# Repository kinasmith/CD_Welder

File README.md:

##Capacitive Discharge Welder

based off of this [project.](http://www.instructables.com/id/Capacitive-Discharge-CD-Welder-for-battery-tabs/) and this [project](http://zeva.com.au/Projects/SpotWelderV2/). 

Included in this repo is the Control code (for arduino Pro Mini), and the PCB files I used. The Capacitor Board is slightly too large for the free version of Eagle (sorry!).

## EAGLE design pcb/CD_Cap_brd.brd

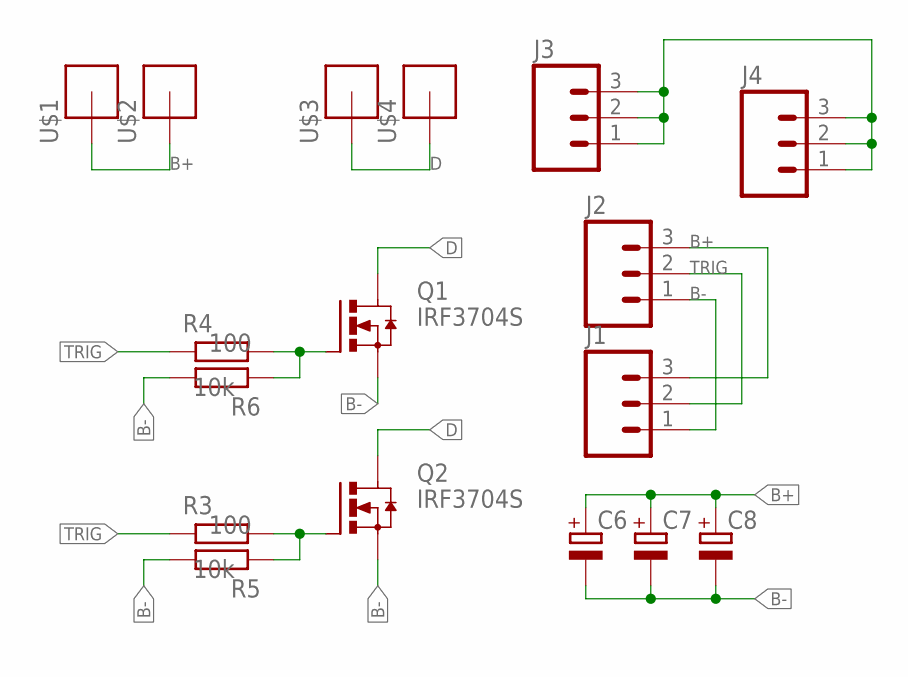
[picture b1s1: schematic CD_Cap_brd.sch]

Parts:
C6, C7, C8: CPOL-EUE10-35; EB35D
J1, J2: M03PTH; 1X03
J3, J4: M03LOCK; 1X03_LOCK
Q1, Q2: IRF3704S; D2PACK
R3, R4: 100; R0603-N
R5, R6: 10k; R0603-N
U$1, U$2, U$3, U$4: BIG_PINHEADX110-32; M6_PINHEAD

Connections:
B+: C6.+, C7.+, C8.+, J1.3, J2.3, U$1.P$1, U$2.P$1
B-: C6.-, C7.-, C8.-, J1.1, J2.1, J3.1, J3.2, J3.3, J4.1, J4.2, J4.3, Q1.3 (S), Q2.3 (S), R5.2, R6.2
D: Q1.2 (D), Q2.2 (D), U$3.P$1, U$4.P$1
unnamed: Q1.1 (G), R4.2, R6.1
unnamed: Q2.1 (G), R3.2, R5.1
TRIG: J1.2, J2.2, R3.1, R4.1

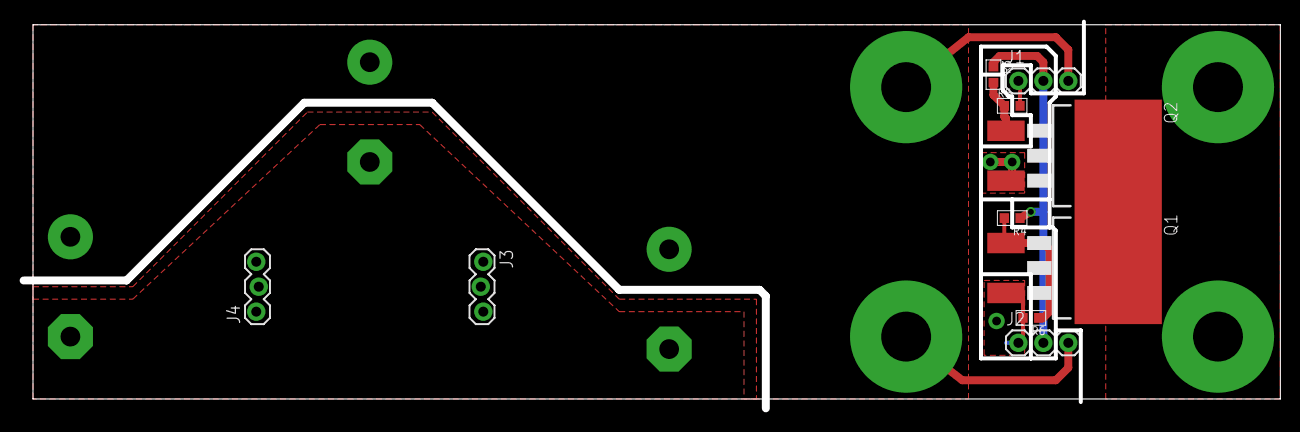
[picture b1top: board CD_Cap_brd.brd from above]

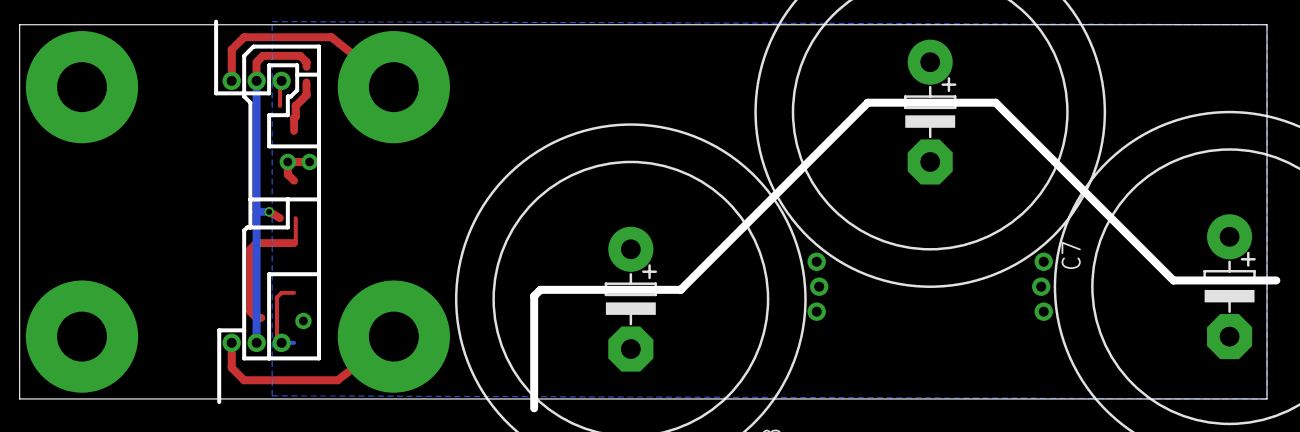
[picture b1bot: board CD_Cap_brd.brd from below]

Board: 2 copper layers, 127.5 x 39.2 mm, 17 parts (3 on the bottom side), 6 nets.

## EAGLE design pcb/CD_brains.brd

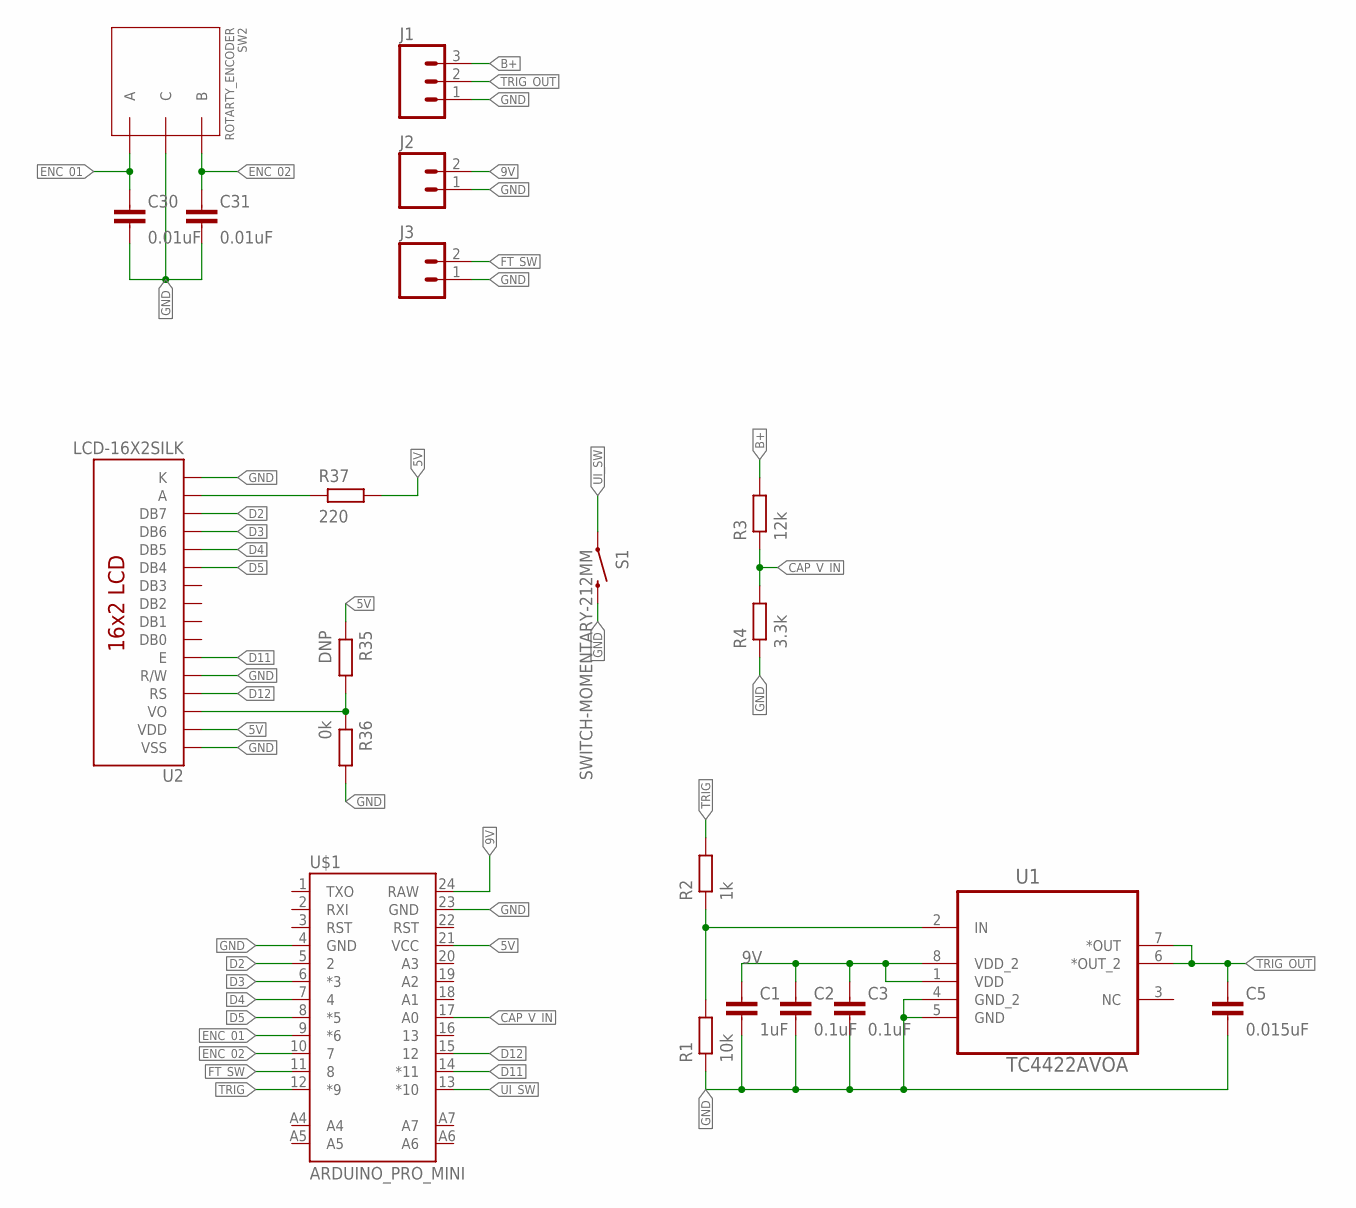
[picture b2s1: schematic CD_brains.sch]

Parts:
C1: 1uF; C0805-N
C2, C3: 0.1uF; C0603-N
C5: 0.015uF; C0603-N
C30, C31: 0.01uF; C0603-N
J1: M03LOCK_NO_SILK; 1X03_LOCK_NO_SILK
J2, J3: M02LOCK; 1X02_LOCK
R1: 10k; R0603-N
R2: 1k; R0603-N
R3: 12k; R0603-N
R4: 3.3k; R0603-N
R35: DNP; R0603-N
R36: 0k; R0603-N
R37: 220; R0603-N
S1: SWITCH-MOMENTARY-212MM; TACTILE-PTH-12MM
SW2: ROTARTY_ENCODER; ROTARY_ENC_PLAIN
U1: TC4422AVOA; SOIC127P600X175-8N
U2: LCD-16X2SILK; LCD-16X2
U$1: ARDUINO_PRO_MINI

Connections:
5V: R35.1, R37.2, U2.2 (VDD), U$1.21 (VCC)
9V: C1.1, C2.1, C3.1, J2.2, U1.1 (VDD), U1.8 (VDD_2), U$1.24 (RAW)
B+: J1.3, R3.2
CAP_V_IN: R3.1, R4.2, U$1.17 (A0)
D2: U2.14 (DB7), U$1.5 (2)
D3: U2.13 (DB6), U$1.6 (*3)
D4: U2.12 (DB5), U$1.7 (4)
D5: U2.11 (DB4), U$1.8 (*5)
D11: U2.6 (E), U$1.14 (*11)
D12: U2.4 (RS), U$1.15 (12)
ENC_01: C30.1, SW2.A, U$1.9 (*6)
ENC_02: C31.1, SW2.B, U$1.10 (7)
FT_SW: J3.2, U$1.11 (8)
GND: C1.2, C2.2, C3.2, C5.2, C30.2, C31.2, J1.1, J2.1, J3.1, R1.1, R4.1, R36.2, S1.3 (2), SW2.C, U1.4 (GND_2), U1.5 (GND), U2.1 (VSS), U2.5 (R/W), U2.16 (K), U$1.4 (GND), U$1.23 (GND)
unnamed: R1.2, R2.1, U1.2 (IN)
unnamed: R37.1, U2.15 (A)
unnamed: R35.2, R36.1, U2.3 (VO)
TRIG: R2.2, U$1.12 (*9)
TRIG_OUT: C5.1, J1.2, U1.6 (*OUT_2), U1.7 (*OUT)
UI_SW: S1.1, U$1.13 (*10)

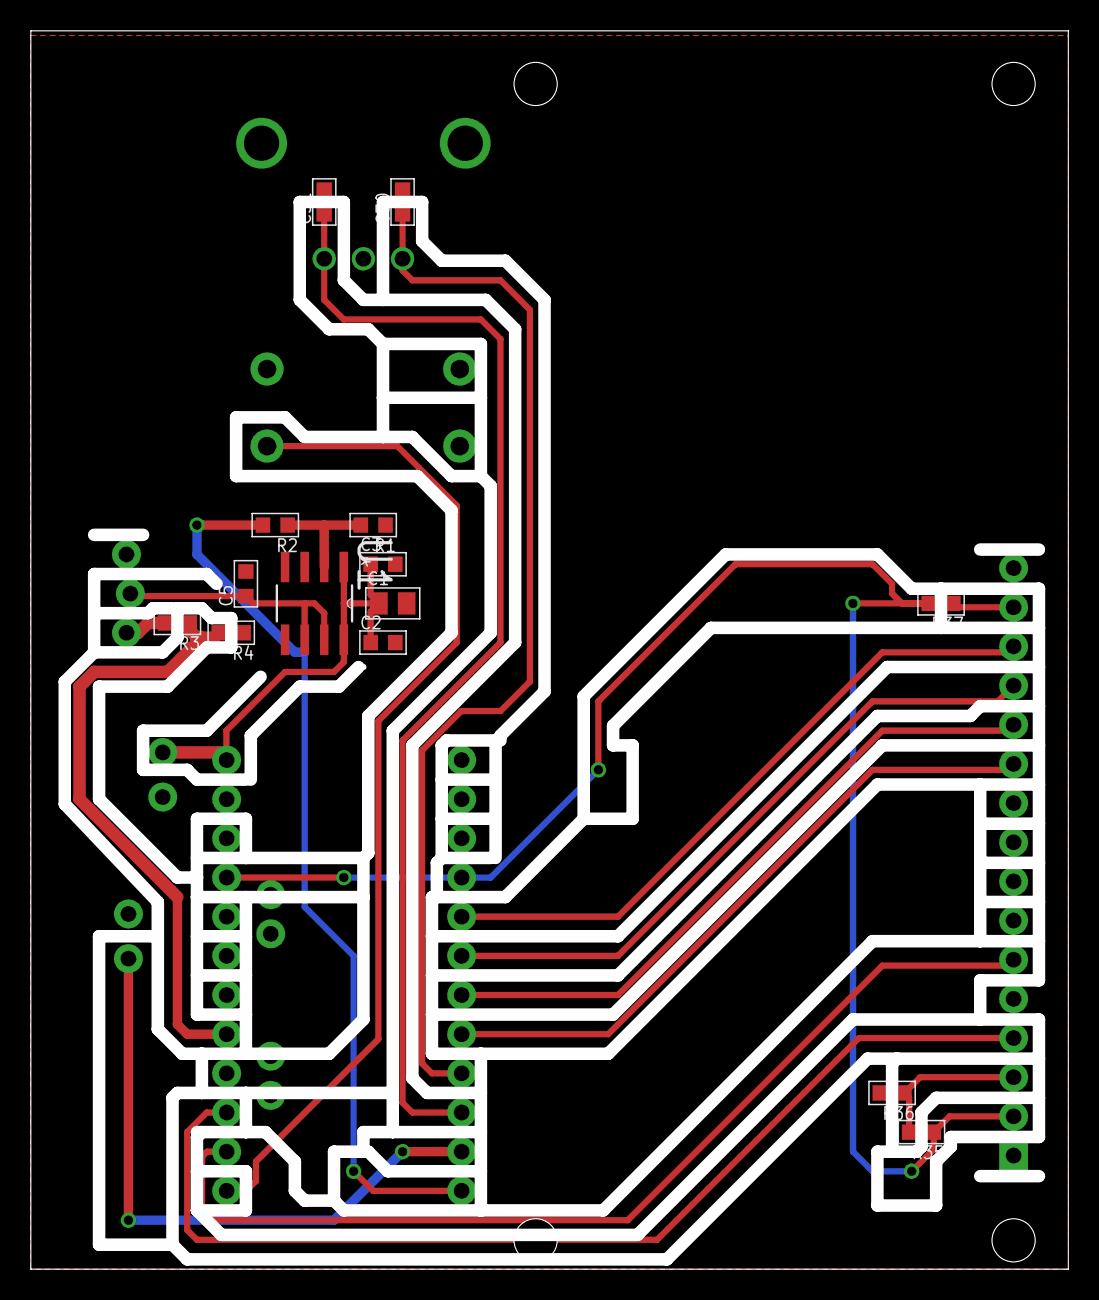
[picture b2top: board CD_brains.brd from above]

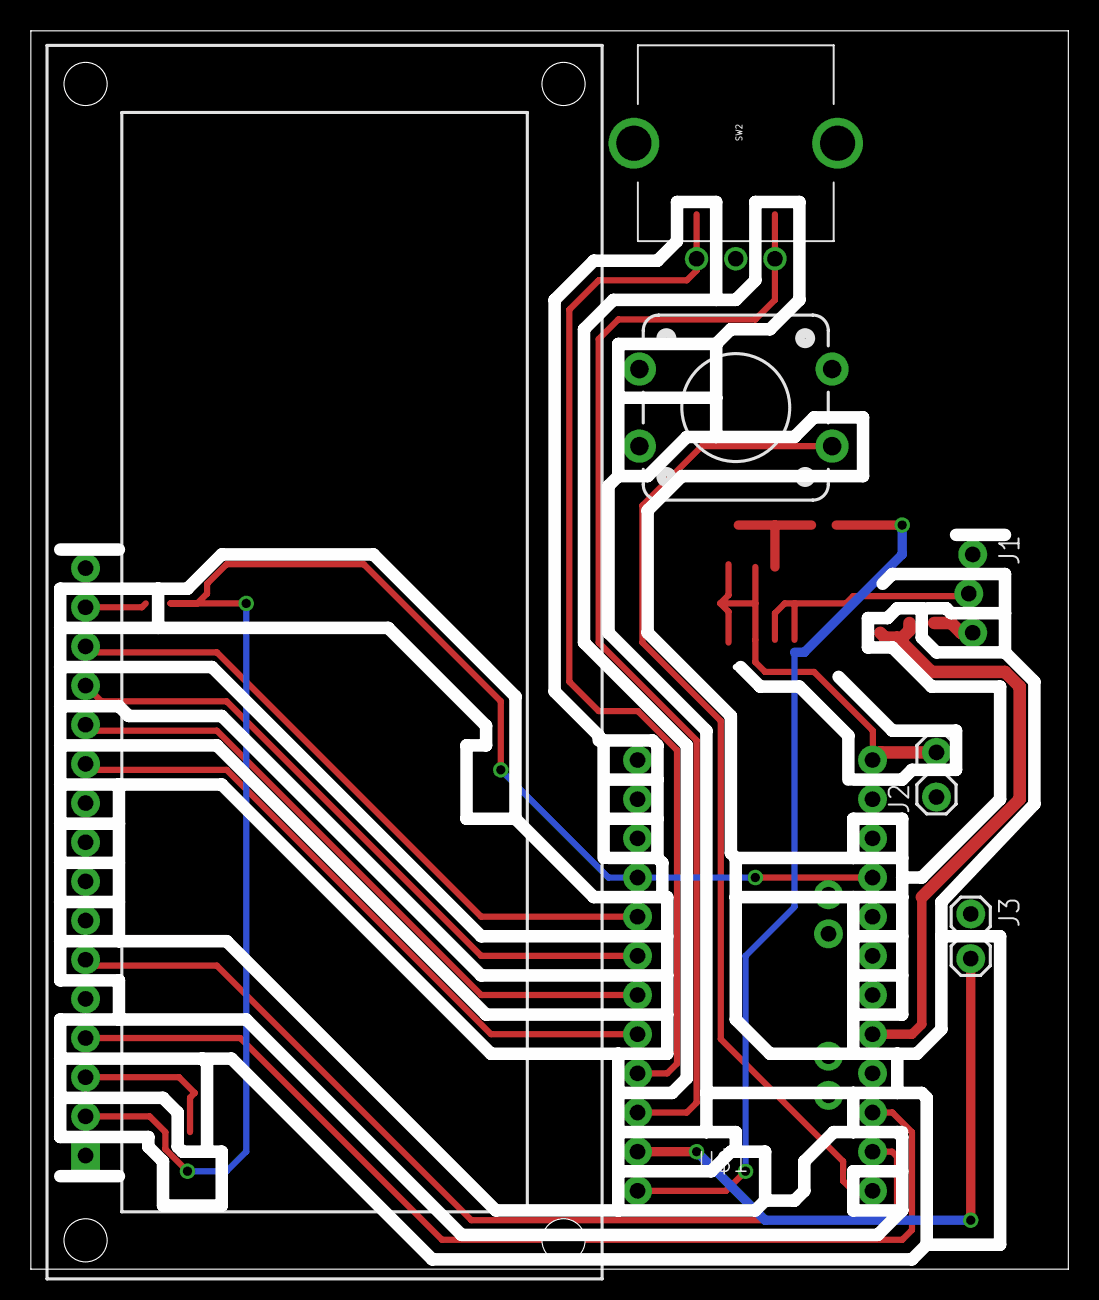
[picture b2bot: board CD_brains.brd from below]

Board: 2 copper layers, 66.5 x 79.5 mm, 21 parts (7 on the bottom side), 20 nets.

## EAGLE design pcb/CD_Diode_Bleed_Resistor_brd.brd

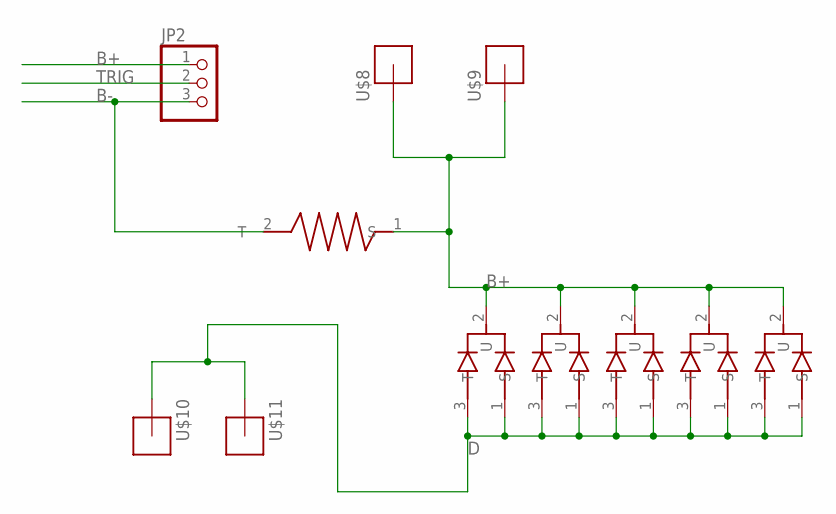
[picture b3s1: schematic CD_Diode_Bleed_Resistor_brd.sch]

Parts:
JP2: PINHD-1X3/90; 1X03/90
U$1, U$2, U$3, U$4, U$5: STTH6002CW; TO-247
U$7: RESISTOR_5W_1INCH; RESISTOR_1INCH_5W
U$8, U$9, U$10, U$11: BIG_PINHEADX110-32; M6_PINHEAD

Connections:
B+: JP2.1, U$1.2 (U), U$2.2 (U), U$3.2 (U), U$4.2 (U), U$5.2 (U), U$7.1 (S), U$8.P$1, U$9.P$1
B-: JP2.3, U$7.2 (T)
D: U$1.1 (S), U$1.3 (T), U$2.1 (S), U$2.3 (T), U$3.1 (S), U$3.3 (T), U$4.1 (S), U$4.3 (T), U$5.1 (S), U$5.3 (T), U$10.P$1, U$11.P$1
TRIG: JP2.2

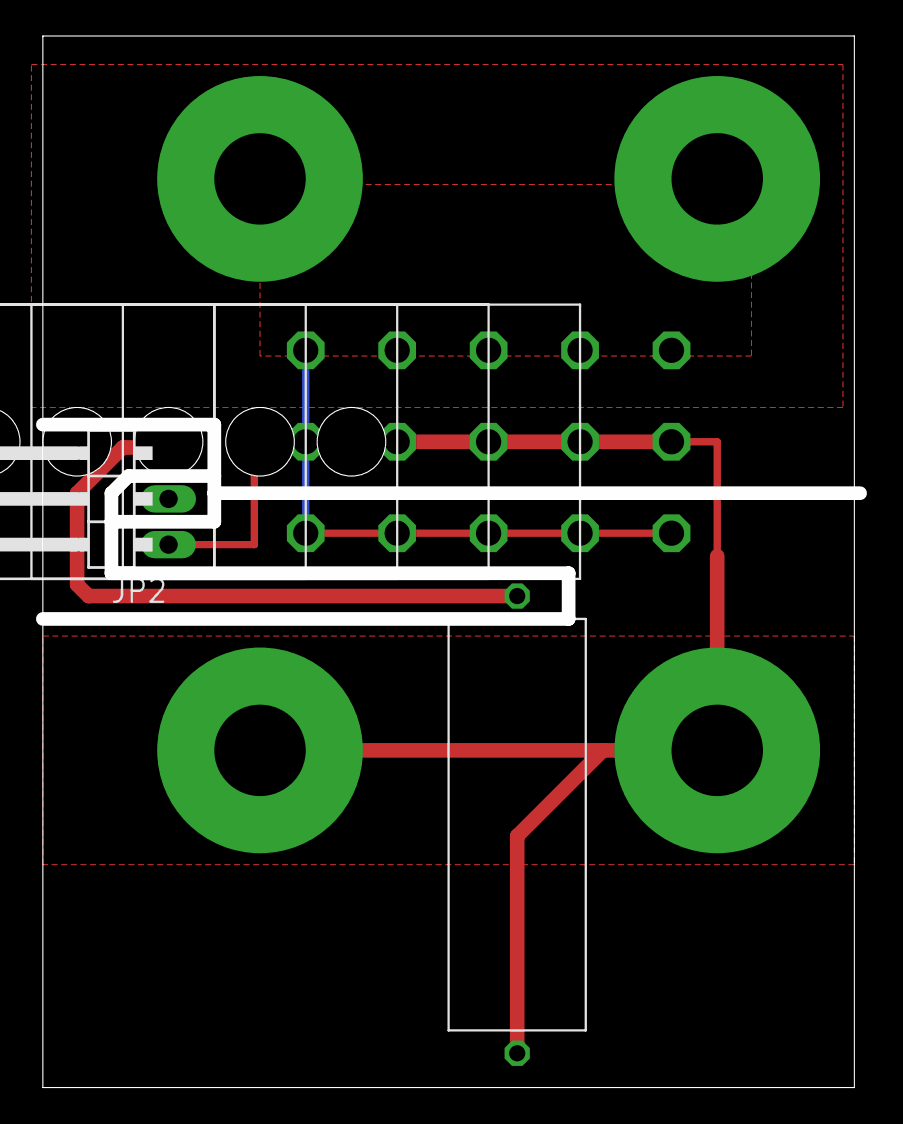
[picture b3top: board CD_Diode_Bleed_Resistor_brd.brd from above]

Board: 2 copper layers, 45.4 x 57.7 mm, 11 parts (0 on the bottom side), 3 nets.

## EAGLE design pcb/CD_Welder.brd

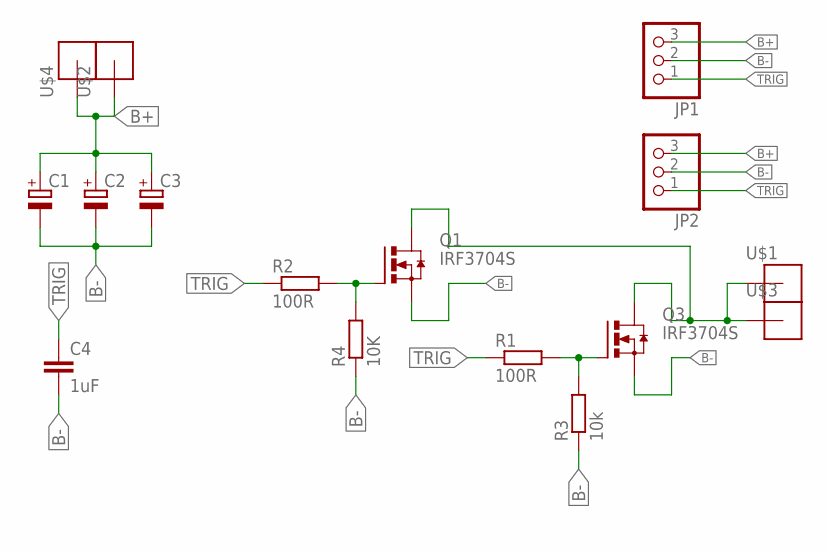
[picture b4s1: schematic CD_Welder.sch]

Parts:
C1, C2, C3: CPOL-EUE10-30; EB30D
C4: 1uF; C1206
JP1, JP2: PINHD-1X3; 1X03
Q1, Q3: IRF3704S; D2PACK
R1, R2: 100R; R1206
R3: 10k; R1206
R4: 10K; R1206
U$1, U$2, U$3, U$4: BIG_PINHEADX1M4; M4_PINHEAD

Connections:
B+: C1.+, C2.+, C3.+, JP1.3, JP2.3, U$2.P$1, U$4.P$1
B-: C1.-, C2.-, C3.-, C4.2, JP1.2, JP2.2, Q1.3 (S), Q3.3 (S), R3.1, R4.1
unnamed: Q1.2 (D), Q3.2 (D), U$1.P$1, U$3.P$1
unnamed: Q1.1 (G), R2.2, R4.2
unnamed: Q3.1 (G), R1.2, R3.2
TRIG: C4.1, JP1.1, JP2.1, R1.1, R2.1

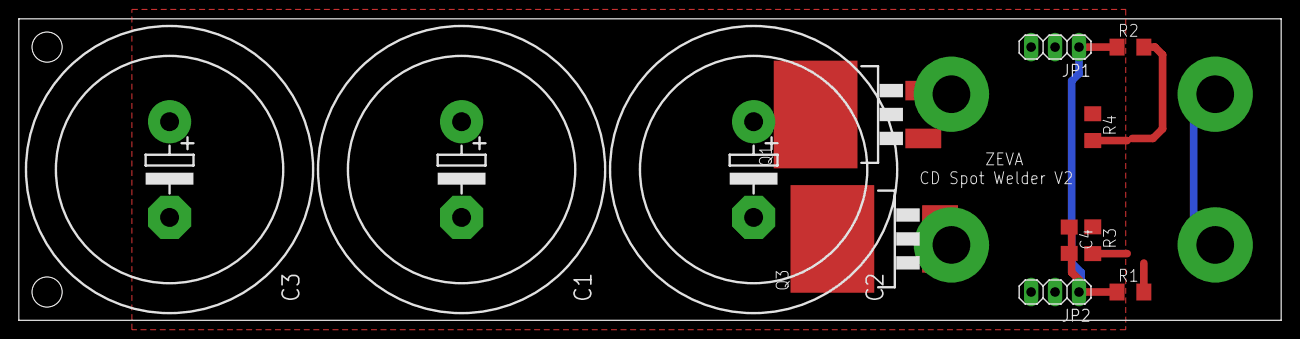
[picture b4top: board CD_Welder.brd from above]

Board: 2 copper layers, 134.0 x 32.0 mm, 16 parts (0 on the bottom side), 6 nets.

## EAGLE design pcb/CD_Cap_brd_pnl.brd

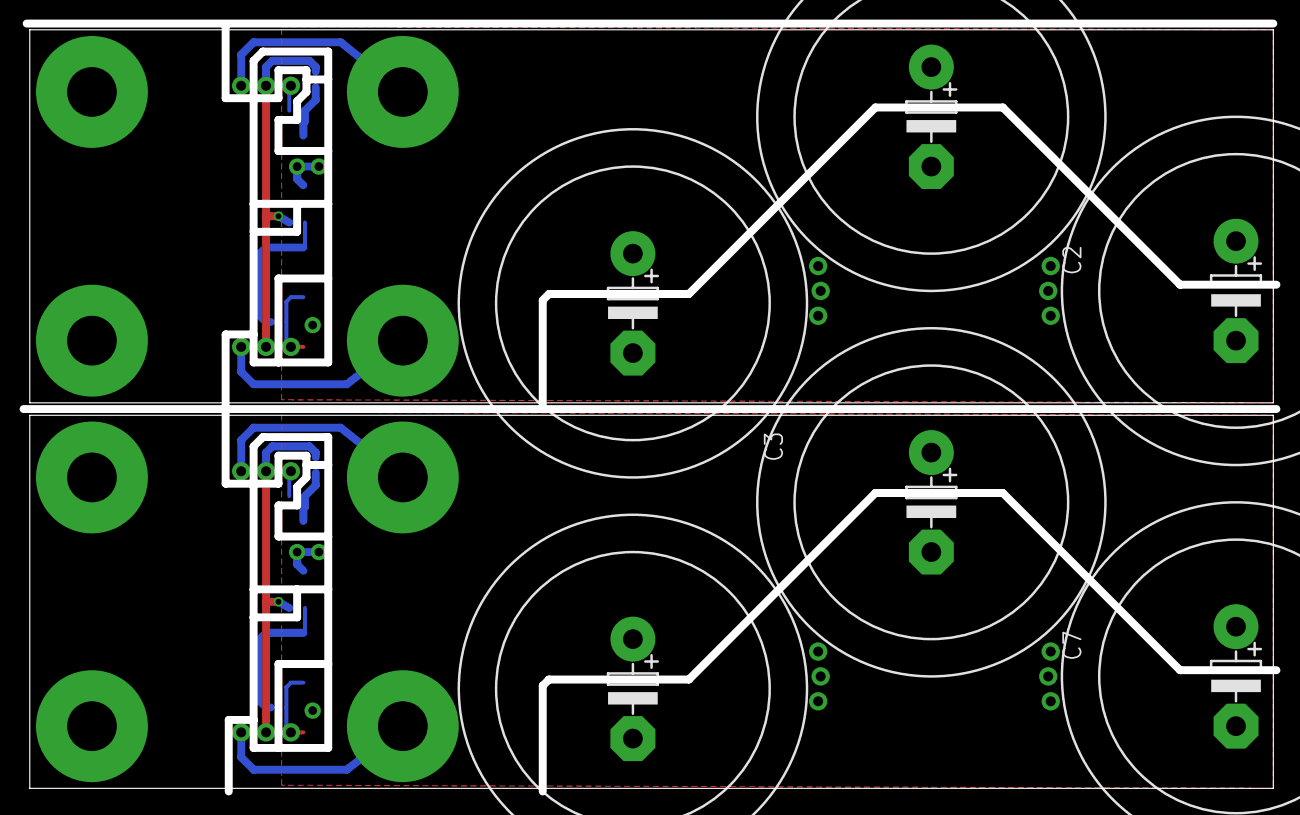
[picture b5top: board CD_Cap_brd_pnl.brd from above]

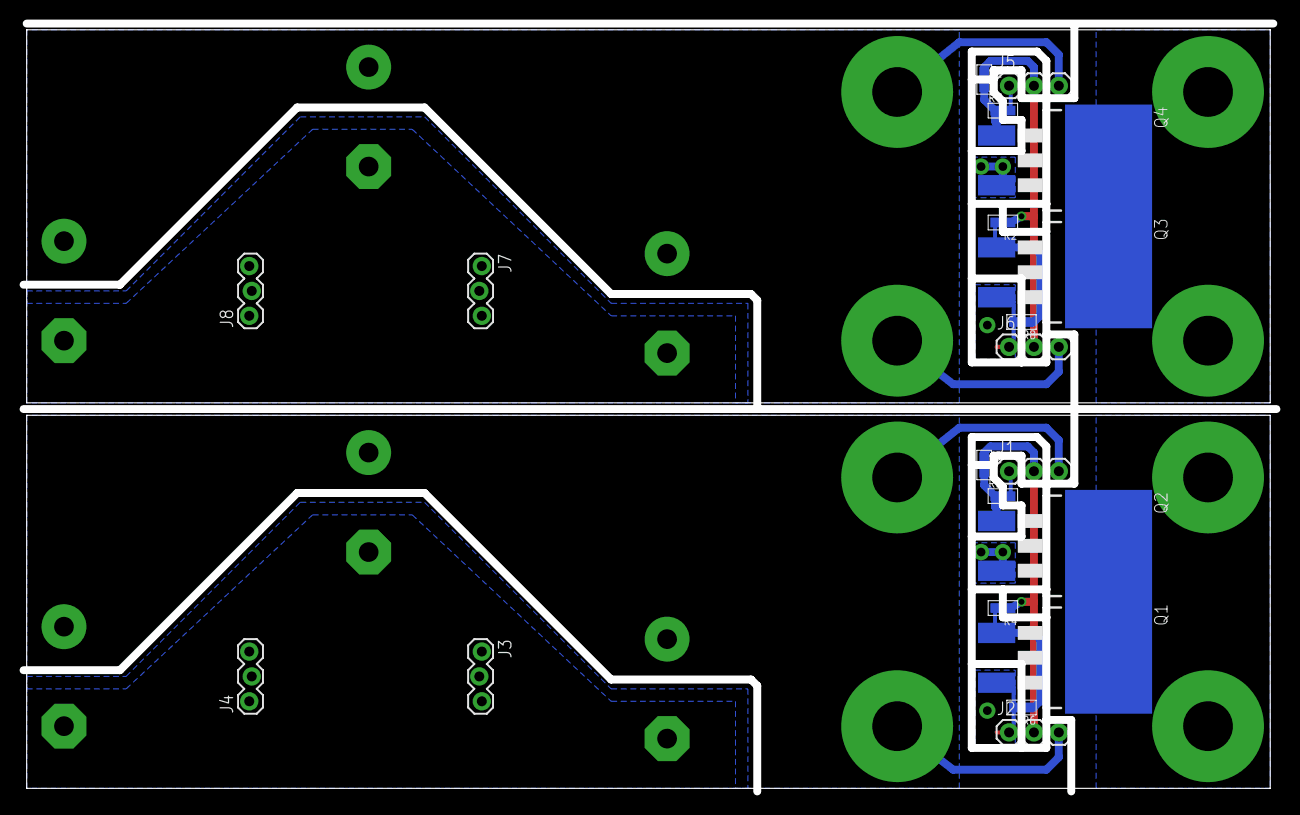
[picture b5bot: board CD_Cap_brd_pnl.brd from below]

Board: 2 copper layers, 128.0 x 78.4 mm, 34 parts (28 on the bottom side), 12 nets.

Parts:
C1, C2, C3, C6, C7, C8: EB35D
J1, J2, J5, J6: 1X03
J3, J4, J7, J8: 1X03_LOCK
Q1, Q2, Q3, Q4: IRF3704S; D2PACK
R1, R2, R3, R4: 100; R0603-N
R5, R6, R7, R8: 10k; R0603-N
U$1, U$2, U$3, U$4, U$5, U$6, U$7, U$8: BIG_PINHEADX110-32; M6_PINHEAD

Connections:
B+: C6.+, C7.+, C8.+, J1.3, J2.3, U$1.P$1, U$2.P$1
B+1: C1.+, C2.+, C3.+, J5.3, J6.3, U$5.P$1, U$6.P$1
B-: C6.-, C7.-, C8.-, J1.1, J2.1, J3.1, J3.2, J3.3, J4.1, J4.2, J4.3, Q1.3, Q2.3, R5.2, R6.2
B-1: C1.-, C2.-, C3.-, J5.1, J6.1, J7.1, J7.2, J7.3, J8.1, J8.2, J8.3, Q3.3, Q4.3, R7.2, R8.2
D: Q1.2, Q2.2, U$3.P$1, U$4.P$1
D1: Q3.2, Q4.2, U$7.P$1, U$8.P$1
unnamed: Q1.1, R4.2, R6.1
unnamed: Q4.1, R1.2, R7.1
unnamed: Q2.1, R3.2, R5.1
unnamed: Q3.1, R2.2, R8.1
TRIG: J1.2, J2.2, R3.1, R4.1
TRIG1: J5.2, J6.2, R1.1, R2.1

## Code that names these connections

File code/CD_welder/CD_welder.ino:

#define ENCODER_DO_NOT_USE_INTERRUPTS

#include "Encoder.h"
#include "LiquidCrystal.h"
#include "Bounce2.h"

const int UI_SW = 10;
const int FT_SW = 8;
const int LED = 13;
const int CAP_V_INPUT = 0;
const int TRIG = 9;
const float div_z1_val = 11990;
const float div_z2_val = 3227;

//vOut = z2/(z1+z2) * vIn

Encoder myEnc(6, 7);
Bounce UI_SW_input = Bounce();
Bounce FT_SW_input = Bounce();
LiquidCrystal lcd(12, 11, 5, 4, 3, 2);

int pulse1Time = 100;
int dwellTime = 100;
int pulse2Time = 100;

float capVoltage = 0;

const int numReadings = 10;  // use this value to determine the size of the readings array.
int voltageReadings[numReadings];      // the readings from the analog input
int voltageReadIndex = 0;              // the index of the current reading
float voltageTotal = 0;                  // the running total
float voltageAverage = 0.0;            // the average
float voltageAverageOld = 0.0;          // the old voltage average reading

boolean voltageSteady = false;    //boolean to monitor whether the voltage is fluctuating - a weld can only be performed when the voltage is stable
int weldComplete = 1;

char* statusText[2] = {"Stabalising volts", "*Ready to weld*"};  // text for the screen to indicate readiness for welding
int  statusTextNum = 0;

int displayUpdateInterval = 500;
long lastUpdate = 0;

int positionCounter = 0;
long encoderPosition  = 100;

void setup() {
  Serial.begin(9600);
  pinMode(LED, OUTPUT);
  pinMode(TRIG, OUTPUT);
  pinMode(UI_SW, INPUT_PULLUP);
  pinMode(FT_SW, INPUT_PULLUP);
  UI_SW_input.attach(UI_SW);
  UI_SW_input.interval(5);
  FT_SW_input.attach(FT_SW);
  FT_SW_input.interval(5);

  lcd.begin(16, 2);
  lcd.print("Electrocution!");
  delay(1000);
  lcd.cursor();
}

void loop() {
  UI_SW_input.update();
  FT_SW_input.update();
  capVoltage = (analogRead(CAP_V_INPUT) / 1024.0 * 5.0) / (div_z2_val / (div_z1_val + div_z2_val));
  if (UI_SW_input.fell()) {
    positionCounter++;
    positionCounter %= 3;
  }
  if (FT_SW_input.fell()) {
    weldSchedule();
  }
  updateDisplay();
  updateEncoder();
}

void updateDisplay() {
  if (millis() > lastUpdate + displayUpdateInterval) {
    lcd.clear();
    lcd.setCursor(0, 0);
    lcd.print("p1");
    lcd.setCursor(3, 0);
    lcd.print(pulse1Time);

    lcd.setCursor(0, 1);
    lcd.print("p2");
    lcd.setCursor(3, 1);
    lcd.print(pulse2Time);

    lcd.setCursor(7, 0);
    lcd.print("dw");
    lcd.setCursor(10, 0);
    lcd.print(dwellTime);

    lcd.setCursor(7, 1);
    lcd.print("cV");
    lcd.setCursor(10, 1);
    lcd.print(capVoltage);
    switch (positionCounter) {
      case 0:
        lcd.setCursor(2, 0);
        break;
      case 1:
        lcd.setCursor(2, 1);
        break;
      case 2:
        lcd.setCursor(9, 0);
        break;
    }
    lastUpdate = millis();
  }
}

void updateEncoder() {
  long newPos = myEnc.read();
  if (newPos != encoderPosition) {
    encoderPosition = newPos;
    switch (positionCounter) {
      case 0:
        pulse1Time = encoderPosition / 4;
        break;
      case 1:
        pulse2Time = encoderPosition / 4;
        break;
      case 2:
        dwellTime = encoderPosition / 4;
        break;
    }
  }
}

void weldSchedule() {
  digitalWrite(TRIG, HIGH);
  delay(pulse1Time/10);
  digitalWrite(TRIG, LOW);
  delay(dwellTime/10);
  digitalWrite(TRIG, HIGH);
  delay(pulse2Time/10);
  digitalWrite(TRIG, LOW);
}

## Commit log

2016-06-28 bunch of circuit stuff done
2016-06-29 almost ready for FAB
2016-06-29 first circuit Fab: Success
2016-07-09 finished the circuits etc.
2016-07-09 initial commit for Code
2016-07-09 cleanup
2016-07-10 finished code. Removed the Diode/Resistor Block...was causing mosfets to latch on
2016-07-12 added to the .gitignore
2016-07-12 removed temp files
2016-07-12 fixed CD BRAINS Inconsistencies
2016-07-12 minor stuff

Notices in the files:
parts and their libraries:
SparkFun-Connectors: Licensing: Creative Commons ShareAlike 4.0 International - https://creativecommons.org/licenses/by-sa/4.0
